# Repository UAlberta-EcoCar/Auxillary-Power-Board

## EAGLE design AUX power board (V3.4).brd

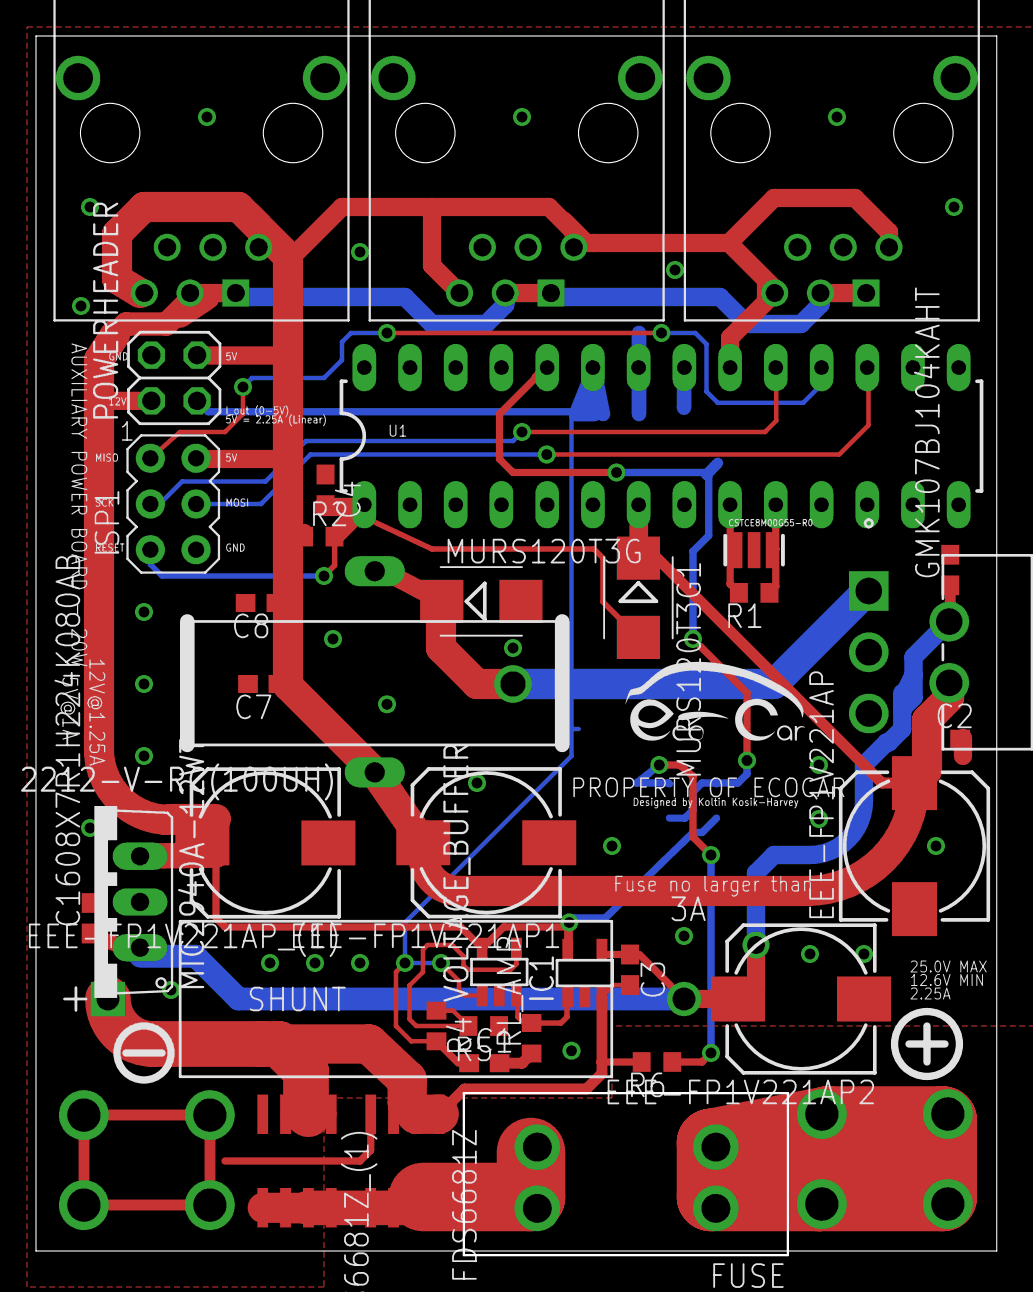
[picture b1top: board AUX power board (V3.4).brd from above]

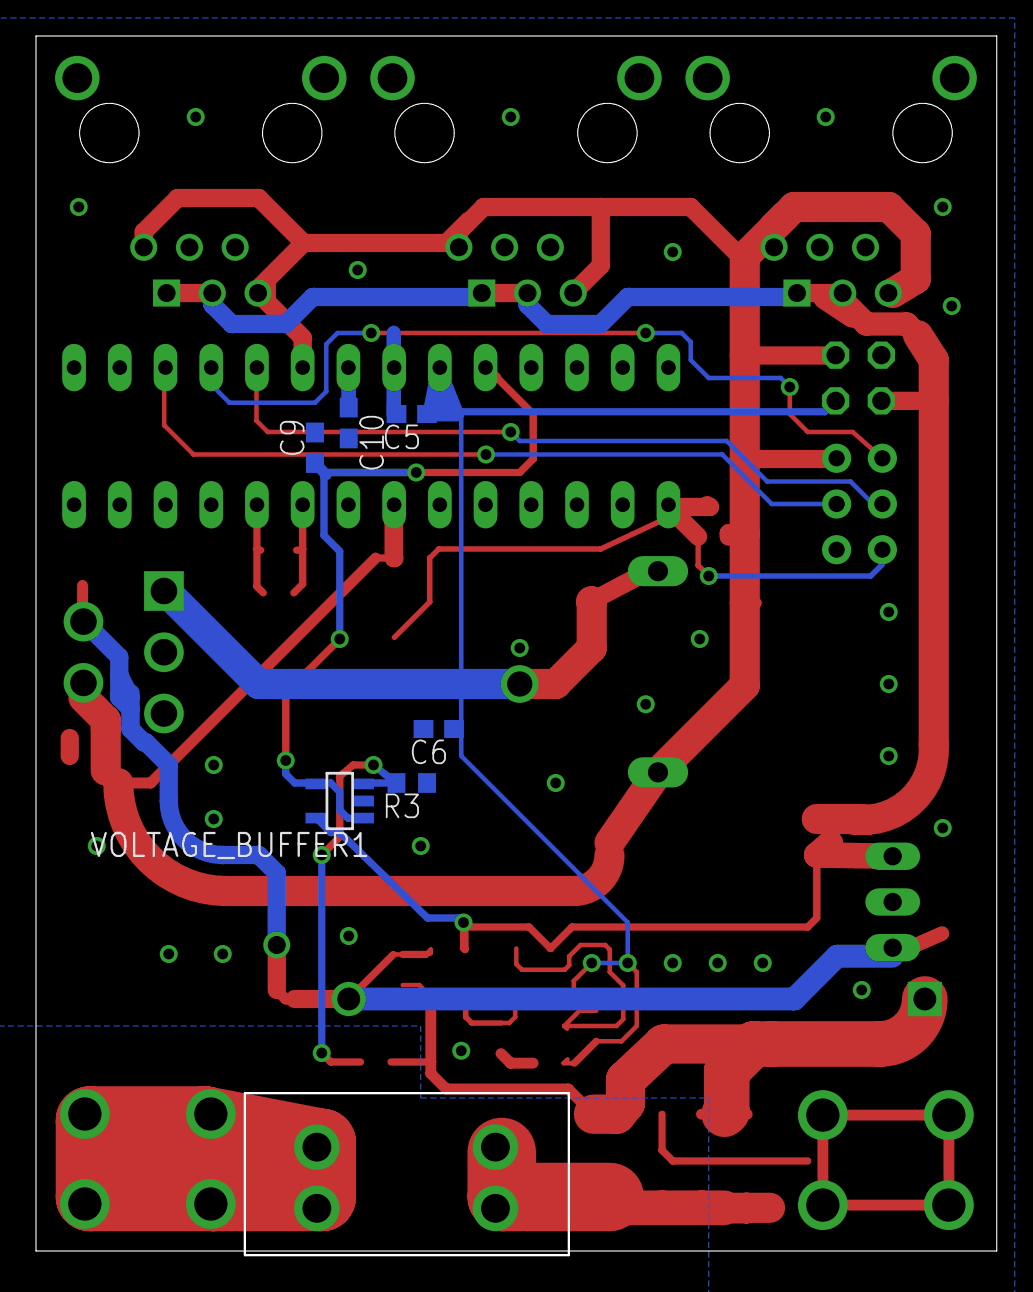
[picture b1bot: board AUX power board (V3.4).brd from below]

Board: 2 copper layers, 53.4 x 67.5 mm, 45 parts (6 on the bottom side), 20 nets.

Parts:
5V_REGULATOR: LM2595T-5.0/NOPB; T05D
15FR005E: 15FR005E; RES_15
2212-V-RC(100UH): SFT1030
C1, C3, C5, C6, C7, C8, C9: 2.2uF; C0603
C2, C4, C10: 0.1uF; C0603
C1608X7R1H224K080AB: 0.22uF; C0603
CSTCE8M00G55-R0: CSTCE16M0V53-R0; RESONATOR
EEE-FP1V221AP, EEE-FP1V221AP1, EEE-FP1V221AP2, EEE-FP1V221AP_(1): 220uF; 175TMP-0808
FDS6681Z, FDS6681Z_(1): SO-08
GMK107BJ104KAHT: 0.1uF; C0603
IC1: INA138; SOT23-5
ISP1: AVRISP-6; AVRISP
MIC2940A-12WT: 7805TV; TO220V
MINIBLADE: 3568
MURS120T3G, MURS120T3G1: MBRS130LT3; SMB
POWERHEADER: 2X02
R1: 1M; R0603
R2: 4.7k; R0603
R3, R5: 10k; R0603
R4, R6: 40k; R0603
RL_AMP: 442k; R0603
U1: ATMEGA328P_PDIP; DIL28-3
U$1: LOGO
U$3, U$4, U$5: 5555140-6; 1734723-1_RJ11
U$6, U$7: SCREW-8191
VOLTAGE_BUFFER, VOLTAGE_BUFFER1: OPA340N; SOT23-5

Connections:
BATTERY_IN_UNFUSED+: MINIBLADE.L1, MINIBLADE.L2, U$6.P$1, U$6.P$2, U$6.P$3, U$6.P$4
FUSED_BATTERY_IN+: 15FR005E.1, C3.2, FDS6681Z.1, FDS6681Z.2, FDS6681Z.3, FDS6681Z_(1).1, FDS6681Z_(1).2, FDS6681Z_(1).3, IC1.3, R6.2
GND: 5V_REGULATOR.3, 5V_REGULATOR.5, C1.2, C2.2, C4.1, C5.2, C6.2, C7.2, C8.2, C9.2, C10.2, C1608X7R1H224K080AB.2, CSTCE8M00G55-R0.2, EEE-FP1V221AP.-, EEE-FP1V221AP1.-, EEE-FP1V221AP2.-, EEE-FP1V221AP_(1).-, FDS6681Z.4, FDS6681Z_(1).4, GMK107BJ104KAHT.2, IC1.2, ISP1.6, MIC2940A-12WT.2, MURS120T3G.A, POWERHEADER.4, R3.1, R5.1, RL_AMP.1, U1.8, U1.22, U$3.5, U$3.6, U$3.SH1, U$3.SH2, U$4.5, U$4.6, U$4.SH1, U$4.SH2, U$5.5, U$5.6, U$5.SH1, U$5.SH2, U$7.P$1, U$7.P$2, U$7.P$3, U$7.P$4, VOLTAGE_BUFFER.2, VOLTAGE_BUFFER1.2
INPUT_UNREG: 5V_REGULATOR.2, 15FR005E.2, C3.1, C1608X7R1H224K080AB.1, EEE-FP1V221AP2.+, GMK107BJ104KAHT.1, IC1.4, MIC2940A-12WT.1
MEASUREMENT_OUT: C1.1, C5.1, C6.1, POWERHEADER.1, R4.2, U1.23, VOLTAGE_BUFFER.1
MISO: ISP1.1, U1.18
MMM: FDS6681Z.5, FDS6681Z.6, FDS6681Z.7, FDS6681Z.8, FDS6681Z_(1).5, FDS6681Z_(1).6, FDS6681Z_(1).7, FDS6681Z_(1).8, MINIBLADE.R1, MINIBLADE.R2
MOSI: ISP1.4, U1.17
unnamed: 5V_REGULATOR.1, 2212-V-RC(100UH).2, MURS120T3G.C
unnamed: R4.1, R5.2, VOLTAGE_BUFFER.4
unnamed: IC1.1, RL_AMP.2, VOLTAGE_BUFFER.3
unnamed: C9.1, U1.24, VOLTAGE_BUFFER1.1, VOLTAGE_BUFFER1.4
unnamed: R3.2, R6.1, VOLTAGE_BUFFER1.3
unnamed: C10.1, U1.21
unnamed: CSTCE8M00G55-R0.1, R1.2, U1.9
unnamed: CSTCE8M00G55-R0.3, R1.1, U1.10
OUTPUT_5REG: 5V_REGULATOR.4, 2212-V-RC(100UH).1, C2.1, C7.1, C8.1, EEE-FP1V221AP.+, EEE-FP1V221AP1.+, ISP1.2, MURS120T3G1.C, POWERHEADER.3, R2.1, U1.7, U1.20, U$3.3, U$3.4, U$4.3, U$4.4, U$5.3, U$5.4
OUTPUT_12REG: EEE-FP1V221AP_(1).+, IC1.5, MIC2940A-12WT.3, POWERHEADER.2, U$3.1, U$3.2, U$4.1, U$4.2, U$5.1, U$5.2, VOLTAGE_BUFFER.5, VOLTAGE_BUFFER1.5
RESET: C4.2, ISP1.5, MURS120T3G1.A, R2.2, U1.1
SCK: ISP1.3, U1.19

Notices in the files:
parts and their libraries:
SparkFun-DigitalIC: Licensing: Creative Commons ShareAlike 4.0 International - https://creativecommons.org/licenses/by-sa/4.0
COPYRIGHT: Copyright C 2015 Accelerated Designs. All rights reserved
